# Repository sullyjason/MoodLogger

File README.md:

# MoodLogger

> **Attribution note:** This README (state documentation, roadmap) and the [Proposed v1 architecture](#proposed-v1-architecture-) section were drafted by **Claude (Fable 5)** on 2026-07-07 and updated as the design converged (part selection finalized 2026-07-10 with **Claude (Opus 4.8)**), based on the KiCad files in this repo, the project motivation, and the Picoclick-C3 reference project. Sections contributed by Claude are marked with 🤖. Hardware design decisions, part orders, prototypes, and project direction by Silvan Roth.

A tiny, battery-powered button logger. Press one of (at least) four buttons and the device wakes up, appends *which button was pressed at what time* to a CSV file, and goes back to sleep. To get the data, you plug the device into any USB host (cable or docking station) and it shows up as an ordinary USB flash drive — no companion app, no driver, no cloud. Grab the CSV, done.

## Design goals

- **≥ 4 buttons**, each press logged as `timestamp, button` to a CSV file
- **Wake on button press, sleep otherwise** — the device spends almost all of its life asleep
- **Battery life measured in months**: recharging should rarely, ideally almost never, be necessary
- **Host-agnostic data access**: the device enumerates as USB mass storage (a flash drive), so any OS can read the CSV without extra software
- **Accurate timestamps** from a dedicated RTC that keeps time even while the MCU sleeps

## Current state

Two prototype PCB revisions exist, both built around a **Seeed Studio XIAO ESP32-S3** module. They differ only in the RTC chip. Both are functional as prototypes but share one critical flaw (see [Known problems](#known-problems)).

### Common to both boards

- **MCU**: XIAO ESP32-S3 (U1) — provides USB-C, LiPo charging, and deep sleep
- **4 tactile buttons** (SW1–SW4, C&K PTS125) on XIAO pins D0–D3, each with a 10 k pull-up and 1 k series resistor, used as wake-up sources
- **I²C RTC** on D4/D5 (SDA/SCL)
- **CR1216 coin cell** (BT1) as RTC backup so time survives even when the main battery is empty
- **SPDT slide switch** (SW5) in the battery line as a hard power switch
- Main power from a LiPo cell on the XIAO's battery pads

### Version A — DS3231 (`EmotionTracker_DS32/`)

Board silkscreen: *EmotionLog v0 8.2025*

- **DS3231M** (U2, SOIC-16): temperature-compensated RTC with internal oscillator — very accurate, no external crystal needed, but comparatively power-hungry

### Version B — PCF8523 (`EmotionTracker_PCF8523/`)

- **PCF8523T** (U3, SOIC-8) with an external 32.768 kHz crystal (Y1) — much lower current draw than the DS3231, at the cost of needing the crystal and being less accurate over temperature
- Adds a status **LED** (D1), an extra small push button (SW6), and **BATin/BATout solder pads** in the battery path for measuring battery current / inserting protection circuitry
- `Dummy device/` contains a mechanical dummy PCB of the same outline for enclosure fitting

### Firmware (`Firmware/`)

Only a bring-up sketch exists so far: `Mood_track_v0/Mood_track_v0.ino` is a WS2812B/FastLED color-cycle test. The actual logging firmware (RTC, deep sleep, CSV writing, USB mass storage) has not been written yet.

## Known problems

**No battery over-discharge protection.** The XIAO ESP32-S3 has a charging circuit but no discharge cutoff, so when the device sits unused, the quiescent draw slowly pulls an unprotected LiPo below its safe minimum voltage and permanently damages it. This has already killed one battery. Nothing on either PCB revision protects against this.

**The XIAO is oversized for the job.** A full ESP32-S3 module with WiFi/BLE is overkill for "log a timestamp and sleep", and its deep-sleep and regulator overhead works against the battery-life goal.

## Roadmap

1. **Software safety first** (works on existing boards): monitor battery voltage from firmware and put the device into its lowest-power shutdown state below a cutoff threshold (with hysteresis so it doesn't oscillate near the limit). On the PCF8523 board the BATin/BATout pads can be used to hook up voltage sensing. This only *mitigates* the problem — even in deepest sleep the board still draws a few µA, so a fully drained device left on the shelf long enough can still damage the cell.
2. **Hardware protection**: add a proper battery protection IC (over-discharge cutoff) to the next board revision, or use protected cells in the meantime.
3. **Custom v1 design**: move away from the XIAO to a leaner MCU (the ATSAMD21G18) with a Picoclick-style soft power latch and native USB mass-storage, designed from the start around the goals above — see [Proposed v1 architecture](#proposed-v1-architecture-) below. Parts are ordered.

## Proposed v1 architecture 🤖

*Section author: Claude (Fable 5, refined with Opus 4.8), 2026-07-07 / 2026-07-10. Based on the boards above and the [Picoclick-C3](https://github.com/makermoekoe/Picoclick-C3) reference project (fork in `Reference Projects/`). Parts are selected and ordered but not yet built or bench-verified — treat as a design proposal, not a validated design.*

### Core idea: soft power latch instead of deep sleep

The key technique to adopt from the Picoclick is its **soft-latching power circuit**: between presses the MCU is not asleep, it is completely unpowered. A button press physically connects the battery to the regulator; the firmware's first act is to hold that connection via a latch GPIO, it logs the event, then releases the latch and the device switches itself off. The Picoclick C3 reaches **< 200 nA idle** this way — roughly three orders of magnitude below the XIAO's deep sleep — and it doubles as the discharge-protection strategy: a device that draws almost nothing cannot slowly kill its LiPo. A dedicated protection IC remains as the hard backstop.

### Why the ATSAMD21G18 (not the RP2040)

Both were considered — the deciding factor was PCB simplicity for a first custom board that may be partly hand-assembled:

- **Leaded package:** the SAMD21 is a TQFP-48 (0.5 mm, gullwing leads) — hand-solderable and inspectable. The RP2040 is a QFN-56 (0.4 mm, leadless + thermal pad) that effectively needs stencil + hot-air.
- **Fewer mandatory parts:** the SAMD21 has 256 KB internal flash and does **crystal-less USB** (clock recovery off the USB frame), so it needs no boot-flash and no crystal. The RP2040 has no internal flash (external QSPI flash is mandatory just to boot) and needs a 12 MHz crystal.
- **Native USB either way:** both enumerate cleanly as USB mass storage. (The Picoclick's own ESP32-C3 does *not* — its USB is a fixed Serial/JTAG peripheral — which is why its MCU was not reused.)

The RP2040 remains a reasonable alternative (faster boot for the latch, larger storage headroom); it just makes the board harder. The nRF52840 is the single-chip option if avoiding external flash matters more than assembly ease.

### Chosen parts (ordered)

| Block | Part | Notes |
|---|---|---|
| MCU | **ATSAMD21G18A** (TQFP-48) | 256 KB flash / 32 KB RAM, native USB, crystal-less USB via clock recovery |
| RTC | **RV-3028-C7** | ~45 nA, internal crystal, ±1 ppm; runs on the always-on rail so time survives with the MCU off. (DS3231M / PCF8523 are the higher-draw fallbacks proven on the existing boards) |
| Data storage | **W25Q32JVSSIM** (SOIC-8, 4 MB) | External SPI NOR for the FAT/CSV volume. Chosen over internal-flash-only for write endurance (~100 k vs ~25 k erase cycles) — each logged press is one FAT-metadata write, so endurance, not capacity, is the limit |
| Battery protection | **BQ29700DSER** | Over-discharge / over-current cutoff — the hard backstop for the failure that killed the prototype battery. Controller only: **needs an external dual N-channel MOSFET** (e.g. FS8205) in the cell's ground path |
| 3.3 V LDO | **AP2112K-3.3** | Sits *after* the latch, so its ~55 µA quiescent is irrelevant (only powered when the device is awake). Regulates the 3.0–4.2 V cell down to a SAMD21-safe 3.3 V |
| Charger | MCP73831-class | Charge current set by R_prog for the chosen small cell |
| Latch + button OR | P-FET high-side switch + Schottky diode-OR | Clone the Picoclick C3T latch topology (in the submodule) |

### Buttons, wake, and logging flow

Each of the four buttons does double duty: all are diode-ORed (Schottky) into the latch enable, so any press powers the board, and each also drives its own sense GPIO with a small RC hold so firmware can still read *which* button fired after boot. USB VBUS feeds the same latch OR, so plugging into any host wakes the device.

- **Log event**: boot → grab latch → read RTC over I²C → append `timestamp,button` to CSV (FatFs on NOR flash) → release latch.
- **USB attached**: enumerate as USB MSC exposing the FAT volume; pause logging while mounted.
- **Setting the clock without an app**: the firmware reads the modification timestamp of a marker file (e.g. the user saves an empty `settime.txt` to the drive) — FAT directory entries carry the host's local time, so any OS can set the RTC just by writing a file. Set-on-flash as baseline.

### Power budget (estimate)

A log event costs roughly 1 µAh (~30 mA for ~100 ms); 20 presses/day is ~0.5 mAh/month. Standby is dominated by the latch leakage plus the protection IC's quiescent draw (sub-µA). Even a 100 mAh cell lasts multiple years and is realistically limited by self-discharge — with the protection IC cutting the cell off safely at the end instead of destroying it.

### Key design notes (SAMD21)

Captured so the board doesn't have to relearn them:

- **`VDDCORE` is a regulator output** — decouple it to ground with 1 µF and connect *nothing* else. Tying it to 3.3 V is the classic dead-SAMD21 mistake.
- **No crystals.** Crystal-less USB (enable USBCRM in firmware) plus the external RV-3028 for timekeeping means neither a 12 MHz nor a 32.768 kHz crystal is needed.
- **Power the RV-3028 from the raw/always-on rail** (ahead of the latch) so it keeps time while the MCU is off; put the I²C pull-ups on the *switched* 3.3 V so they don't leak from the battery in standby.
- **BQ29700 needs external FETs.** It's a protection *controller* — pair it with a dual N-channel MOSFET in the cell's ground path; it does not switch current on its own.
- **AP2112K goes after the latch**, where its ~55 µA quiescent is a non-issue. Never put it on the always-on rail.
- **The latch is the only non-textbook subcircuit** — clone the Picoclick C3T topology from the submodule rather than inventing one, and give it enough RC hold to survive the SAMD21 boot time before firmware grabs the latch GPIO.
- **Fixed USB/SWD pins:** USB D−/D+ on PA24/PA25, SWD on PA30/PA31. I²C and SPI go on any valid SERCOM pads (confirm against the pinmux table).

## Repository layout

| Path | Contents |
|---|---|
| `EmotionTracker_DS32/` | KiCad 8 project, DS3231 revision (`production/` has JLCPCB gerbers, BOM, placement files) |
| `EmotionTracker_PCF8523/` | KiCad 8 project, PCF8523 revision + mechanical dummy board (`production/` as above) |
| `Firmware/Mood_track_v0/` | Arduino bring-up sketch (LED test only, no logging yet) |
| `Reference Projects/` | Picoclick-C3-Logger (git submodule, fork of makermoekoe/Picoclick-C3) — reference for the latch circuit and battery protection |
| `docs/` | Architecture diagrams |

## History

The concept was first prototyped on a breadboard with a XIAO ESP32-S3 and a DS3231 RTC module. That prototype worked, but the lack of discharge protection destroyed the battery — which is what motivated the roadmap above.

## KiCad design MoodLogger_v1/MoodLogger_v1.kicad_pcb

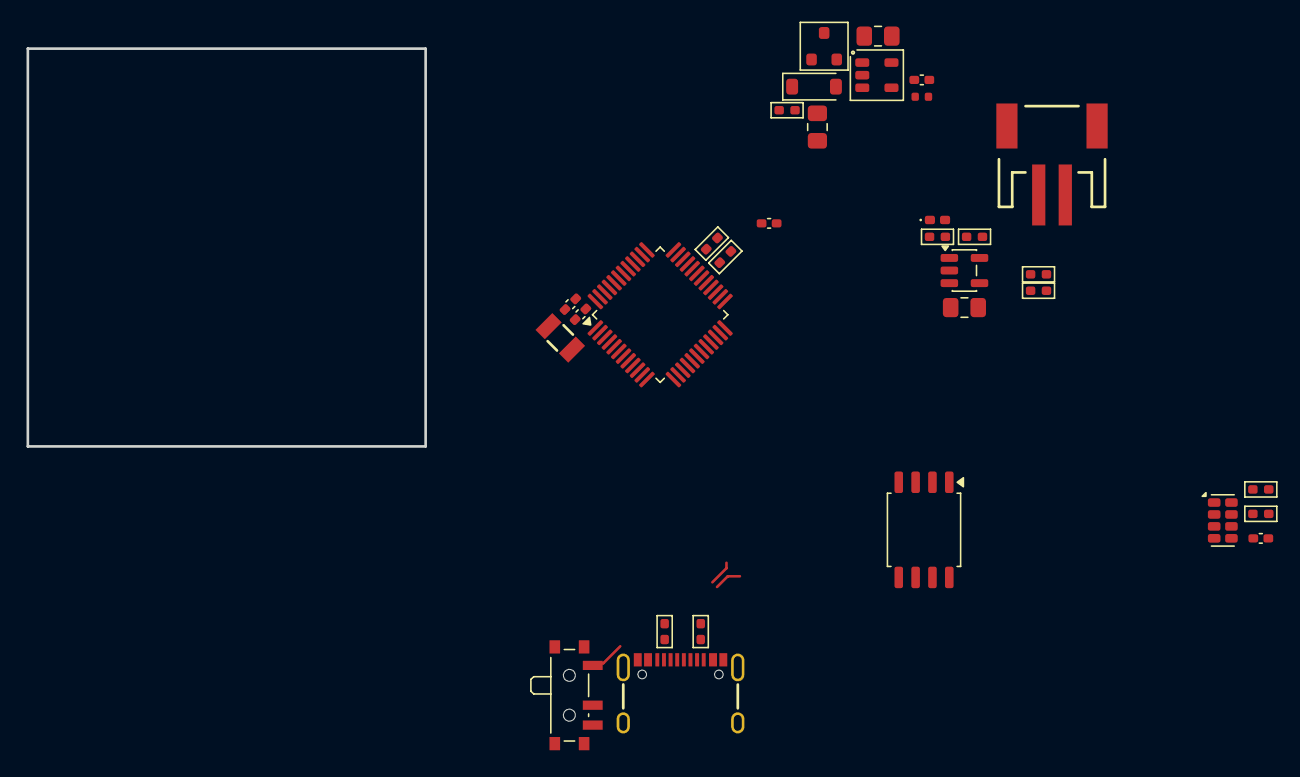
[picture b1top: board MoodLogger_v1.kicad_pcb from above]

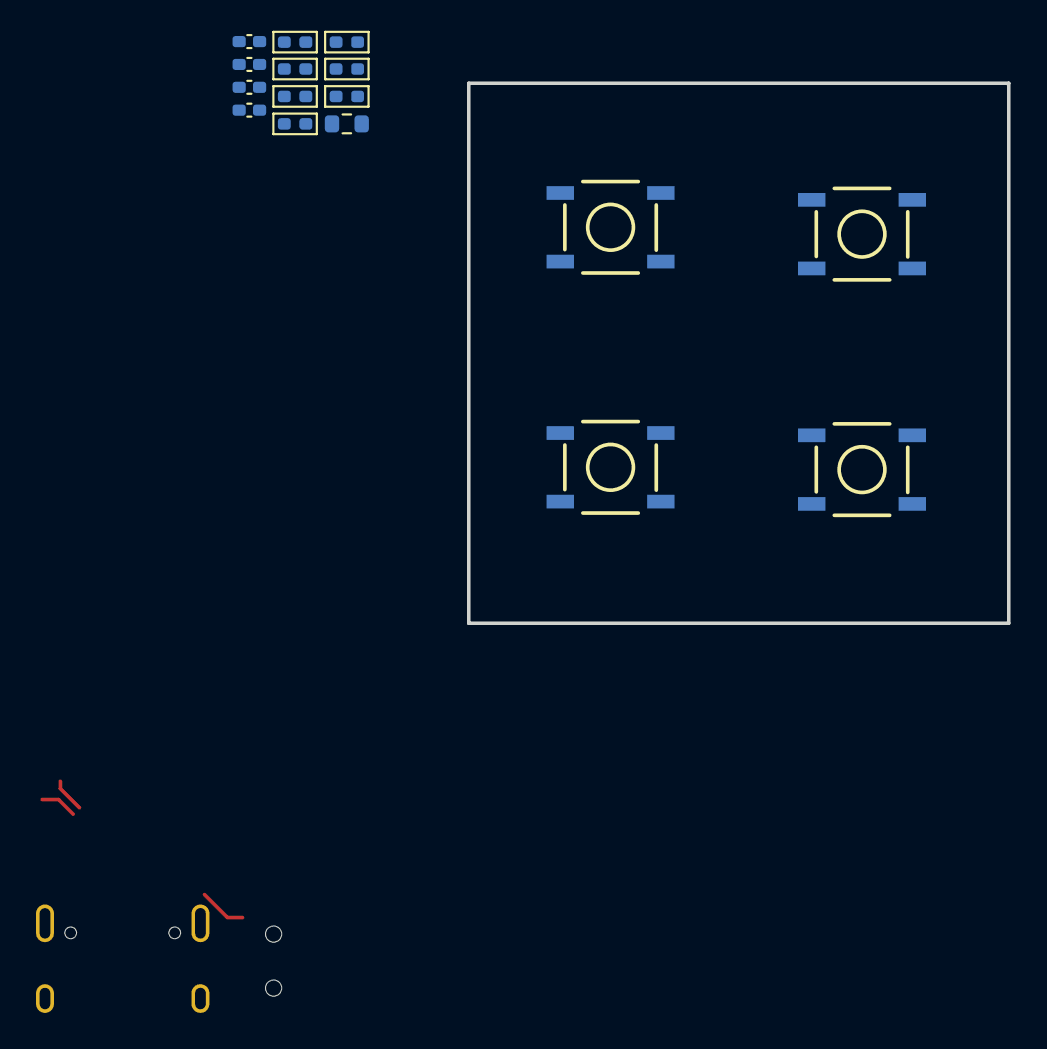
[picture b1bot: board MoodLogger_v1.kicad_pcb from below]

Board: 2 copper layers, 30.0 x 30.0 mm, 48 parts (16 on the bottom side), 35 nets.

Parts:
C1, C10, C15, C16, C17, C18: 1uF; C_0402_1005Metric_Pad0.74x0.62mm_HandSolder
C6: 100nF; C_0402_1005Metric_Pad0.74x0.62mm_HandSolder
C19, C20: 10uF; C_0805_2012Metric_Pad1.18x1.45mm_HandSolder
C21: 10µF; C_0805_2012Metric_Pad1.18x1.45mm_HandSolder
C22, C23: 22pF; C_0402_1005Metric_Pad0.74x0.62mm_HandSolder
CHG2: ORANGE; LED_0402_1005Metric_Pad0.77x0.64mm_HandSolder
D2: MBR120; D_SOD-123
J2: USB_C_Receptacle; USB-C_16
J3: JST_2mm_LiPo; JST_1x02_P2.0mm_Horizontal_SMD
Q1: DMG3415U; SOT-23
R1, R2: 5.1k; R_0402_1005Metric_Pad0.72x0.64mm_HandSolder
R3: 10k; R_0603_1608Metric
R6, R22, R23: 10kΩ; R_0402_1005Metric_Pad0.72x0.64mm_HandSolder
R7: 100Ω; R_0402_1005Metric_Pad0.72x0.64mm_HandSolder
R9, R12, R19: 10k; R_0402_1005Metric_Pad0.72x0.64mm_HandSolder
R10, R11, R20, R21: 1k; R_0402_1005Metric_Pad0.72x0.64mm_HandSolder
R13: 100kΩ; R_0402
R14: 1K; R_0402_1005Metric_Pad0.72x0.64mm_HandSolder
R15: 10K\; R_0402_1005Metric_Pad0.72x0.64mm_HandSolder
R16, R17, R18: 100kΩ; R_0402_1005Metric_Pad0.72x0.64mm_HandSolder
SW2, SW3, SW5, SW6: SW_MEC_5E; Push_SMD_5.2x5.2mm_h2.5mm
SW4: Slide_Switch_SPDT; SW_SPDT_PCM12
U1: ATSAMD21G18A-A; TQFP-48_7x7mm_P0.5mm
U2: RV-3028-C7; MicroCrystal_C7_SON-8_1.5x3.2mm_P0.9mm
U5: AP2112K-3.3TRG1; SOT-23-5
U6: MCP73831T-2ACI/OT; SOT-23-5
U7: W25Q32JVSS; SOIC-8_5.3x5.3mm_P1.27mm
Y1: 32.768kHz; Crystal_SMD_3.2x1.5mm

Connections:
3.3V: C18.1, C19.2, U5.5 (OUT), U7.3 (~WP/IO_{2}), U7.7 (~HOLD/~RESET/IO_{3}), U7.8 (VCC)
+3.3V: R3.1, R9.1, R12.1, R19.1, R22.1, R23.1
/5V_TO_SWITCH: J2.VBUS, SW4.1
BMON: R16.2, R17.1
BUTTON_1: C10.1, R10.1, U1.3 (PA02)
BUTTON_2: C17.1, R21.1, U1.4 (PA03)
BUTTON_3: C15.1, R11.1, U1.9 (PA04)
BUTTON_4: C16.1, R20.1, U1.10 (PA05)
D+: J2.A6 (D+), J2.B6 (D+), U1.34 (PA25)
D-: J2.A7 (D-), J2.B7 (D-), U1.33 (PA24)
FLASH_CS: U1.22 (PA13), U7.1 (~CS)
FLASH_MISO: U1.23 (PA14), U7.2 (DO/IO_{1})
FLASH_MOSI: U1.13 (PA08), U7.5 (DI/IO_{0})
FLASH_SCK: U1.14 (PA09), U7.6 (CLK)
GND: C1.1, C6.2, C10.2, C15.2, C16.2, C17.2, C18.2, C19.1, C20.2, C21.2, C22.2, C23.2, J2.GND, J2.S (SHIELD), J3.1 (-), R1.2, R2.2, R15.2, R16.1, R18.1, SW2.1, SW3.1, SW5.1, SW6.1, U1.5 (GNDANA), U1.18 (GND), U1.35 (GND), U1.42 (GND), U2.5 (VSS), U5.2, U6.2 (VSS), U7.4 (GND)
unnamed: C20.1, D2.1 (C), Q1.2 (S), R13.1, R18.2, U5.1 (IN)
unnamed: J2.A5 (CC1), R1.1
unnamed: J2.B5 (CC2), R2.1
unnamed: R3.2, R10.2, SW2.2
unnamed: R9.2, R11.2, SW5.2
unnamed: R12.2, R20.2, SW3.2
unnamed: R19.2, R21.2, SW6.2
unnamed: C23.1, U1.1 (PA00)
unnamed: C22.1, U1.2 (PA01)
unnamed: C1.2, U1.43 (VDDCORE)
unnamed: R6.2, U2.8 (EVI)
unnamed: R7.2, U2.6 (VBACKUP)
unnamed: R13.2, U5.3 (EN)
unnamed: R15.1, U6.5 (PROG)
unnamed: R14.2, U6.1 (STAT)
SCL: R23.2, U1.32 (PA23), U2.3 (SCL)
SDA: R22.2, U1.31 (PA22), U2.4 (SDA)
VBATT: C21.1, J3.2 (+), Q1.3 (D), R17.2, U6.3 (VBAT)
VBUS: D2.2 (A), Q1.1 (G), SW4.2, U6.4 (VDD)
VDD: C6.1, R6.1, R7.1, U2.7 (VDD)
